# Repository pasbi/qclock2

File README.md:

# qclock2
Code, Schematics, Photos of the WortUhr Hack

The WORTUHR is a clock that displays the current time in form of glowing words.
This is about the German variant.

Note: The instance I got is presumably a cheap copy of a more expensive design https://qlocktwo.com/.

## Original Design

There is a metal cover of size 20cm x 20cm.
25 German words are blanked out.
It has a DC 5V 1A power connector and two buttons (`+`) and (`-`).
The plastic housing is 4 cm thick and encloses the metal sheet completey.
Inside there is a PCB whith 25 LED-groups, one group per word, with varying number of LEDs per group.
There's further two groups with each five LED drivers (transitor and multiple resistors), one IC, a quartz and few other passive components.
After powering the the PCB, the clock displays 12:00 ("ES IST ZWÖLF UHR").
The time can be adjusted using the two buttons.

## Problem

The problem with the original product is that it does reset every time power is disconnected.
That makes it inconvenient to use occasionally.

## Idea

Implement some circuit that synchronizes the time via NTP.

## Implementation

The original driver chip has been unsoldered, the 10 transistors on the board have been soldered to cables and dupont-connectors.

A 8266 and MCP23017 are connected via I²C.
The MCP keeps the time and synchronizes regularly via WIFI and NTP.
Since the watch works at 5V and the 8266 at 3.3V, a two-channel bidirectional logic level converter is required to translate the I²C signals.

Porting the breadboard to a sodered board turned out messy, error-prone and cumbersome.
Ordering a printed PCB seems to be the better choice.

kicad-files can be found in the repo:

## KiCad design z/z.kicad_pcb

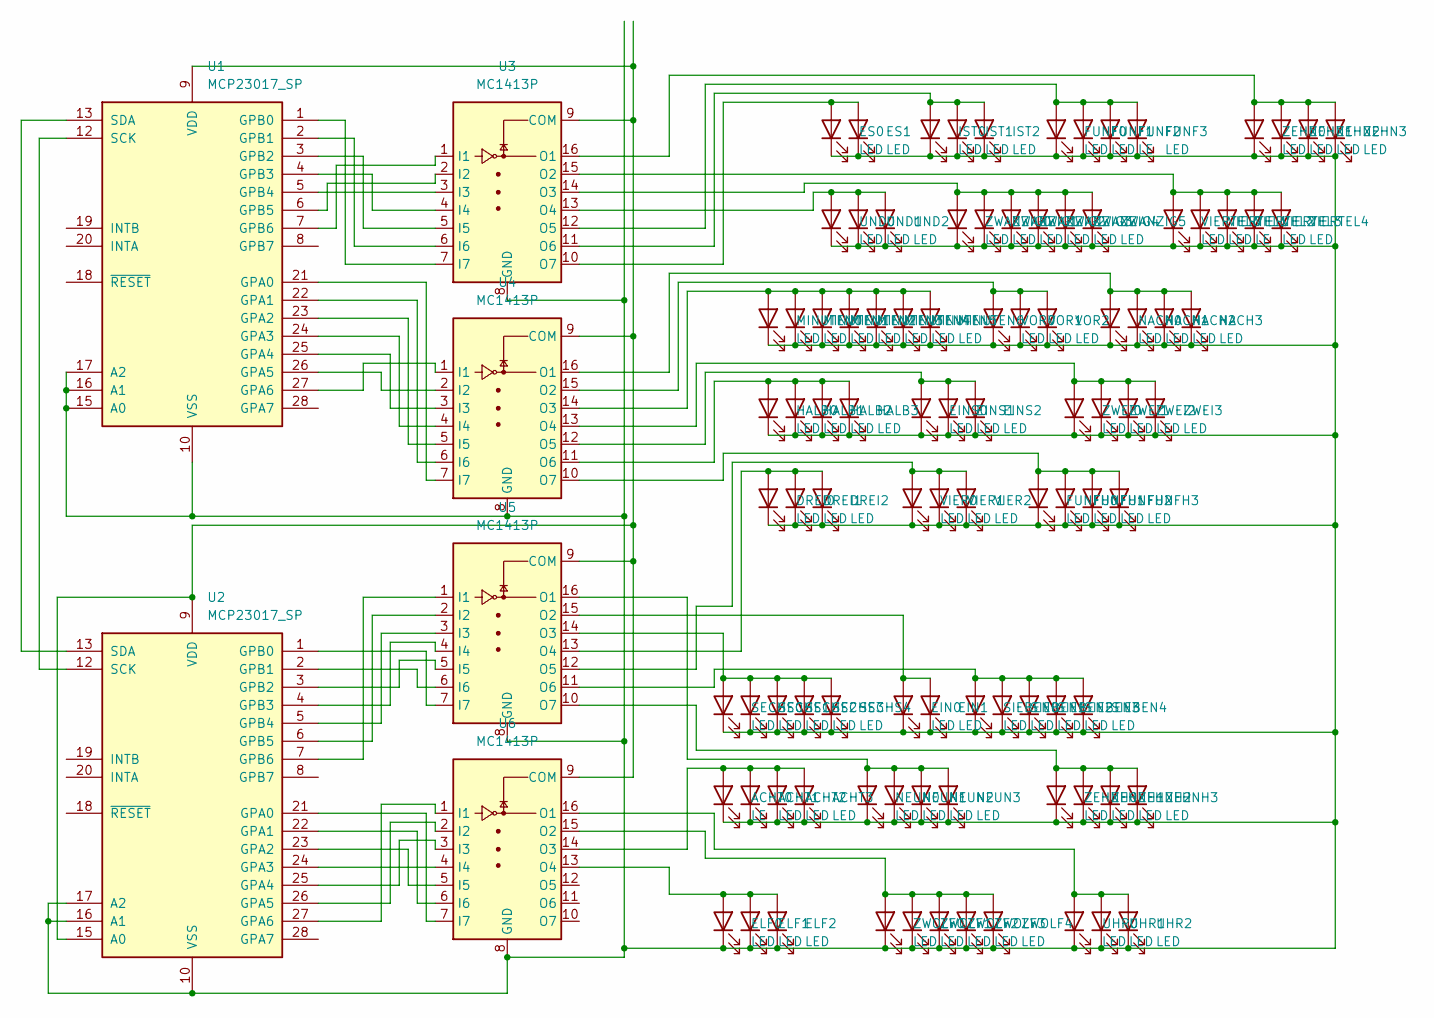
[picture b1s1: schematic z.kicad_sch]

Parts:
ACHT0: LE; LED_D5.0mm_Clear
ACHT1, ACHT2, ACHT3: LED; LED_D5.0mm_Clear
DREI0, DREI1, DREI2: LED; LED_D5.0mm_Clear
EIN0, EIN1: LED; LED_D5.0mm_Clear
EINS0, EINS1, EINS2: LED; LED_D5.0mm_Clear
ELF0, ELF1, ELF2: LED; LED_D5.0mm_Clear
ES0, ES1: LED; LED_D5.0mm_Clear
FUNF0, FUNF1, FUNF3: LED; LED_D5.0mm_Clear
FUNF2: LE; LED_D5.0mm_Clear
FUNFH0, FUNFH1, FUNFH2, FUNFH3: LED; LED_D5.0mm_Clear
HALB0, HALB1, HALB2, HALB3: LED; LED_D5.0mm_Clear
IST0, IST1, IST2: LED; LED_D5.0mm_Clear
MINUTEN0, MINUTEN1, MINUTEN2, MINUTEN3, MINUTEN4, MINUTEN5, MINUTEN6: LED; LED_D5.0mm_Clear
NACH0, NACH1, NACH2, NACH3: LED; LED_D5.0mm_Clear
NEUN0, NEUN1, NEUN2, NEUN3: LED; LED_D5.0mm_Clear
SECHS0, SECHS1, SECHS2, SECHS3, SECHS4: LED; LED_D5.0mm_Clear
SIEBEN0, SIEBEN1, SIEBEN2, SIEBEN3, SIEBEN4: LED; LED_D5.0mm_Clear
U1, U2: MCP23017_SP; DIP-28_W7.62mm
U3, U4, U5, U6: MC1413P; DIP-16_W7.62mm
UHR0, UHR1, UHR2: LED; LED_D5.0mm_Clear
UND0, UND1, UND2: LED; LED_D5.0mm_Clear
VIER0, VIER1, VIER2: LED; LED_D5.0mm_Clear
VIERTEL0, VIERTEL1, VIERTEL3, VIERTEL4: LED; LED_D5.0mm_Clear
VIERTEL2: LE; LED_D5.0mm_Clear
VOR0, VOR1, VOR2: LED; LED_D5.0mm_Clear
ZEHN0, ZEHN1, ZEHN2, ZEHN3: LED; LED_D5.0mm_Clear
ZEHNH0, ZEHNH1, ZEHNH2, ZEHNH3: LED; LED_D5.0mm_Clear
ZWANZIG0, ZWANZIG1, ZWANZIG2, ZWANZIG3, ZWANZIG4, ZWANZIG5: LED; LED_D5.0mm_Clear
ZWEI0, ZWEI1, ZWEI2, ZWEI3: LED; LED_D5.0mm_Clear
ZWOLF0, ZWOLF1, ZWOLF2, ZWOLF3, ZWOLF4: LED; LED_D5.0mm_Clear

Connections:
unnamed: ACHT0.2 (A), ACHT1.2 (A), ACHT2.2 (A), ACHT3.2 (A), U6.14 (O3)
unnamed: DREI0.2 (A), DREI1.2 (A), DREI2.2 (A), U5.13 (O4)
unnamed: EIN0.2 (A), EIN1.2 (A), U5.15 (O2)
unnamed: EINS0.2 (A), EINS1.2 (A), EINS2.2 (A), U4.12 (O5)
unnamed: ELF0.2 (A), ELF1.2 (A), ELF2.2 (A), U6.13 (O4)
unnamed: ES0.2 (A), ES1.2 (A), U3.10 (O7)
unnamed: FUNF0.2 (A), FUNF1.2 (A), FUNF2.2 (A), FUNF3.2 (A), U3.12 (O5)
unnamed: FUNFH0.2 (A), FUNFH1.2 (A), FUNFH2.2 (A), FUNFH3.2 (A), U4.10 (O7)
unnamed: HALB0.2 (A), HALB1.2 (A), HALB2.2 (A), HALB3.2 (A), U4.11 (O6)
unnamed: IST0.2 (A), IST1.2 (A), IST2.2 (A), U3.11 (O6)
unnamed: MINUTEN0.2 (A), MINUTEN1.2 (A), MINUTEN2.2 (A), MINUTEN3.2 (A), MINUTEN4.2 (A), MINUTEN5.2 (A), MINUTEN6.2 (A), U4.14 (O3)
unnamed: NACH0.2 (A), NACH1.2 (A), NACH2.2 (A), NACH3.2 (A), U4.16 (O1)
unnamed: NEUN0.2 (A), NEUN1.2 (A), NEUN2.2 (A), NEUN3.2 (A), U5.16 (O1)
unnamed: SECHS0.2 (A), SECHS1.2 (A), SECHS2.2 (A), SECHS3.2 (A), SECHS4.2 (A), U5.14 (O3)
unnamed: SIEBEN0.2 (A), SIEBEN1.2 (A), SIEBEN2.2 (A), SIEBEN3.2 (A), SIEBEN4.2 (A), U5.11 (O6)
unnamed: U1.3 (GPB2), U3.5 (I5)
unnamed: U1.4 (GPB3), U3.4 (I4)
unnamed: U1.6 (GPB5), U3.2 (I2)
unnamed: U1.9 (VDD), U2.9 (VDD), U2.15 (A0), U3.9 (COM), U4.9 (COM), U5.9 (COM), U6.9 (COM)
unnamed: U1.12 (SCK), U2.12 (SCK)
unnamed: U1.13 (SDA), U2.13 (SDA)
unnamed: U1.22 (GPA1), U4.6 (I6)
unnamed: U1.23 (GPA2), U4.5 (I5)
unnamed: U1.24 (GPA3), U4.4 (I4)
unnamed: U1.25 (GPA4), U4.3 (I3)
unnamed: U1.26 (GPA5), U4.2 (I2)
unnamed: U1.27 (GPA6), U4.1 (I1)
unnamed: U2.1 (GPB0), U5.7 (I7)
unnamed: U2.2 (GPB1), U5.6 (I6)
unnamed: U2.22 (GPA1), U6.6 (I6)
unnamed: U2.23 (GPA2), U6.5 (I5)
unnamed: U2.24 (GPA3), U6.4 (I4)
unnamed: U2.25 (GPA4), U6.3 (I3)
unnamed: U1.7 (GPB6), U3.1 (I1)
unnamed: U1.5 (GPB4), U3.3 (I3)
unnamed: U1.2 (GPB1), U3.6 (I6)
unnamed: U1.1 (GPB0), U3.7 (I7)
unnamed: U1.21 (GPA0), U4.7 (I7)
unnamed: U2.7 (GPB6), U5.1 (I1)
unnamed: U2.6 (GPB5), U5.2 (I2)
unnamed: U2.5 (GPB4), U5.3 (I3)
unnamed: U2.4 (GPB3), U5.4 (I4)
unnamed: U2.3 (GPB2), U5.5 (I5)
unnamed: U5.10 (O7), ZEHNH0.2 (A), ZEHNH1.2 (A), ZEHNH2.2 (A), ZEHNH3.2 (A)
unnamed: U2.27 (GPA6), U6.1 (I1)
unnamed: U2.26 (GPA5), U6.2 (I2)
unnamed: U2.21 (GPA0), U6.7 (I7)
unnamed: U6.16 (O1), UHR0.2 (A), UHR1.2 (A), UHR2.2 (A)
unnamed: U3.13 (O4), UND0.2 (A), UND1.2 (A), UND2.2 (A)
unnamed: U5.12 (O5), VIER0.2 (A), VIER1.2 (A), VIER2.2 (A)
unnamed: U3.15 (O2), VIERTEL0.2 (A), VIERTEL1.2 (A), VIERTEL2.2 (A), VIERTEL3.2 (A), VIERTEL4.2 (A)
unnamed: U4.15 (O2), VOR0.2 (A), VOR1.2 (A), VOR2.2 (A)
unnamed: ACHT0.1 (K), ACHT1.1 (K), ACHT2.1 (K), ACHT3.1 (K), DREI0.1 (K), DREI1.1 (K), DREI2.1 (K), EIN0.1 (K), EIN1.1 (K), EINS0.1 (K), EINS1.1 (K), EINS2.1 (K), ELF0.1 (K), ELF1.1 (K), ELF2.1 (K), ES0.1 (K), ES1.1 (K), FUNF0.1 (K), FUNF1.1 (K), FUNF2.1 (K), FUNF3.1 (K), FUNFH0.1 (K), FUNFH1.1 (K), FUNFH2.1 (K), FUNFH3.1 (K), HALB0.1 (K), HALB1.1 (K), HALB2.1 (K), HALB3.1 (K), IST0.1 (K), IST1.1 (K), IST2.1 (K), MINUTEN0.1 (K), MINUTEN1.1 (K), MINUTEN2.1 (K), MINUTEN3.1 (K), MINUTEN4.1 (K), MINUTEN5.1 (K), MINUTEN6.1 (K), NACH0.1 (K), NACH1.1 (K), NACH2.1 (K), NACH3.1 (K), NEUN0.1 (K), NEUN1.1 (K), NEUN2.1 (K), NEUN3.1 (K), SECHS0.1 (K), SECHS1.1 (K), SECHS2.1 (K), SECHS3.1 (K), SECHS4.1 (K), SIEBEN0.1 (K), SIEBEN1.1 (K), SIEBEN2.1 (K), SIEBEN3.1 (K), SIEBEN4.1 (K), U1.10 (VSS), U1.15 (A0), U1.16 (A1), U1.17 (A2), U2.10 (VSS), U2.16 (A1), U2.17 (A2), U3.8 (GND), U4.8 (GND), U5.8 (GND), U6.8 (GND), UHR0.1 (K), UHR1.1 (K), UHR2.1 (K), UND0.1 (K), UND1.1 (K), UND2.1 (K), VIER0.1 (K), VIER1.1 (K), VIER2.1 (K), VIERTEL0.1 (K), VIERTEL1.1 (K), VIERTEL2.1 (K), VIERTEL3.1 (K), VIERTEL4.1 (K), VOR0.1 (K), VOR1.1 (K), VOR2.1 (K), ZEHN0.1 (K), ZEHN1.1 (K), ZEHN2.1 (K), ZEHN3.1 (K), ZEHNH0.1 (K), ZEHNH1.1 (K), ZEHNH2.1 (K), ZEHNH3.1 (K), ZWANZIG0.1 (K), ZWANZIG1.1 (K), ZWANZIG2.1 (K), ZWANZIG3.1 (K), ZWANZIG4.1 (K), ZWANZIG5.1 (K), ZWEI0.1 (K), ZWEI1.1 (K), ZWEI2.1 (K), ZWEI3.1 (K), ZWOLF0.1 (K), ZWOLF1.1 (K), ZWOLF2.1 (K), ZWOLF3.1 (K), ZWOLF4.1 (K)
unnamed: U3.16 (O1), ZEHN0.2 (A), ZEHN1.2 (A), ZEHN2.2 (A), ZEHN3.2 (A)
unnamed: U3.14 (O3), ZWANZIG0.2 (A), ZWANZIG1.2 (A), ZWANZIG2.2 (A), ZWANZIG3.2 (A), ZWANZIG4.2 (A), ZWANZIG5.2 (A)
unnamed: U4.13 (O4), ZWEI0.2 (A), ZWEI1.2 (A), ZWEI2.2 (A), ZWEI3.2 (A)
unnamed: U6.15 (O2), ZWOLF0.2 (A), ZWOLF1.2 (A), ZWOLF2.2 (A), ZWOLF3.2 (A), ZWOLF4.2 (A)

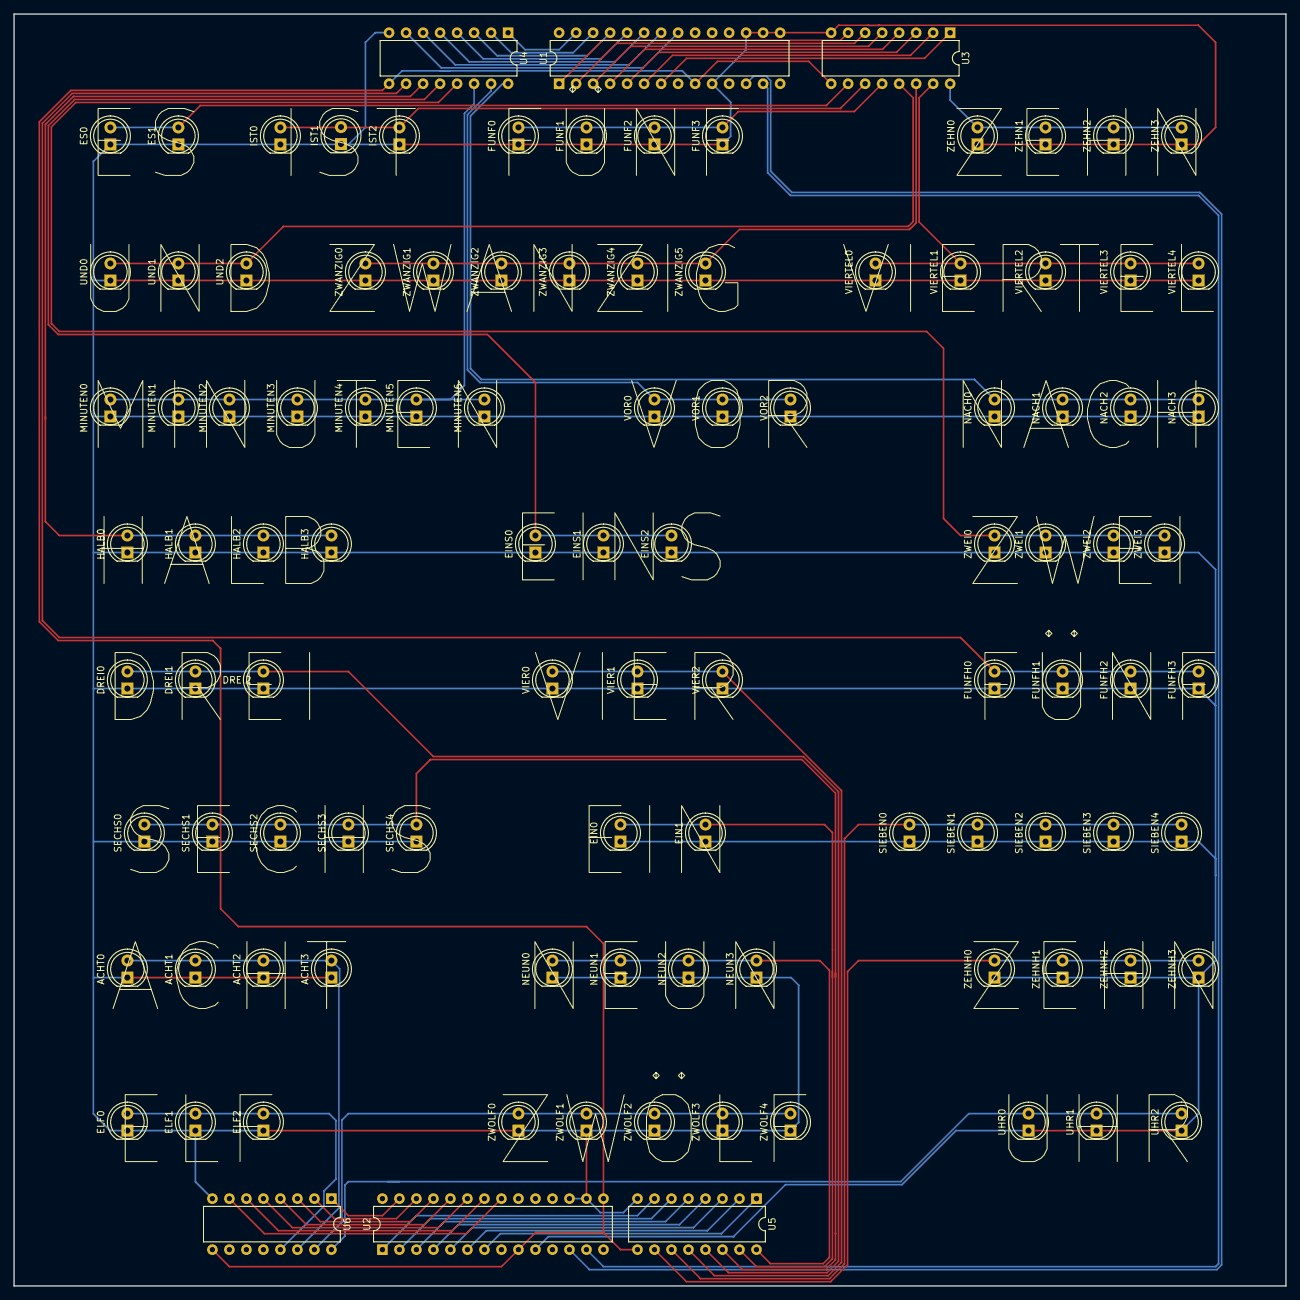
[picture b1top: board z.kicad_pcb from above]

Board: 2 copper layers, 190.0 x 190.0 mm, 103 parts (0 on the bottom side), 57 nets.

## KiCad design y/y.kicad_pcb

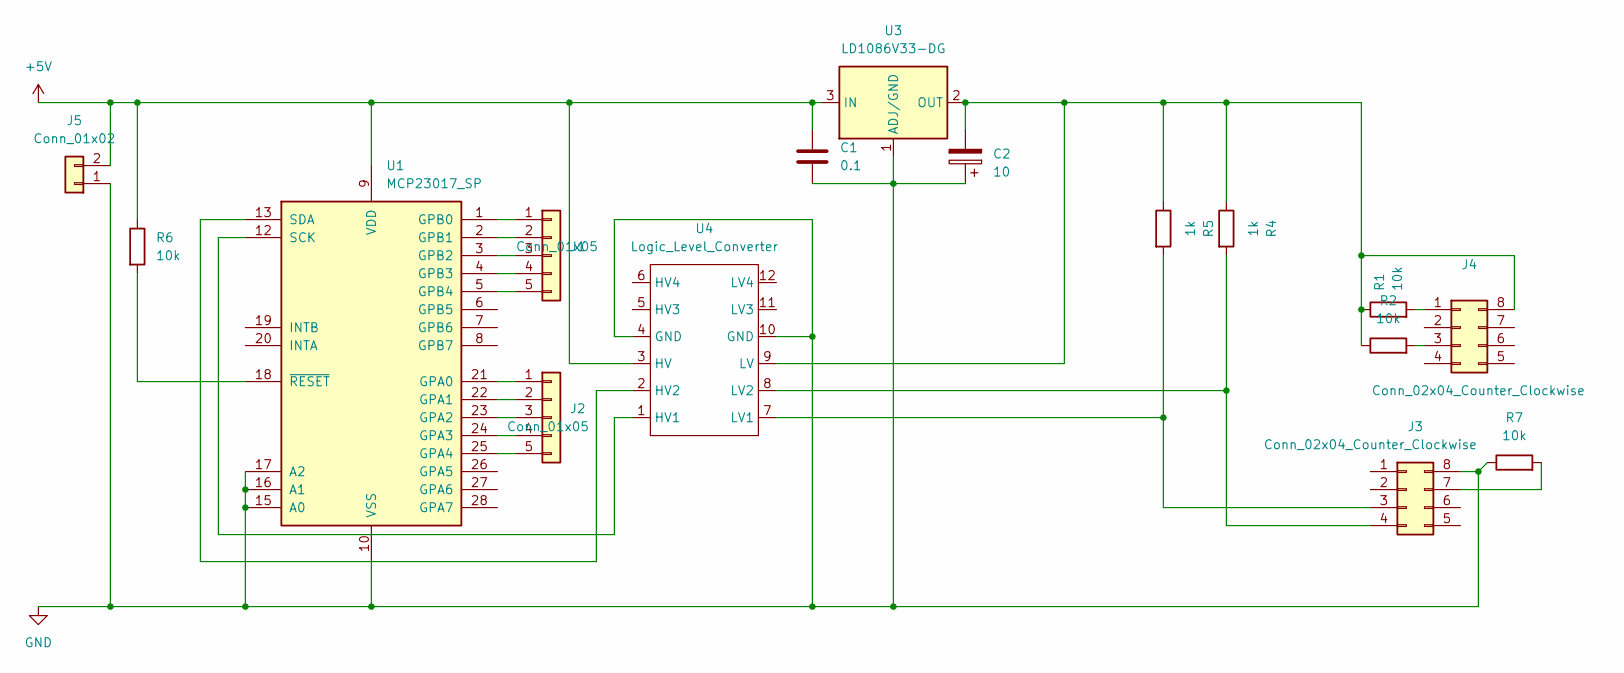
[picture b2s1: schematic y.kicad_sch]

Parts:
C1: 0.1; C_Disc_D11.0mm_W5.0mm_P5.00mm
C2: 10; CP_Radial_Tantal_D4.5mm_P2.50mm
J1, J2: Conn_01x05; PinHeader_1x05_P2.54mm_Vertical
J3, J4: Conn_02x04_Counter_Clockwise; PinSocket_2x04_P2.54mm_Vertical
J5: Conn_01x02; PinSocket_1x02_P2.54mm_Vertical
R1, R2, R6, R7: 10k; R_Axial_DIN0207_L6.3mm_D2.5mm_P7.62mm_Horizontal
R4, R5: 1k; R_Axial_DIN0207_L6.3mm_D2.5mm_P7.62mm_Horizontal
U1: MCP23017_SP; DIP-28_W7.62mm
U3: LD1086V33-DG; TO-220-3_Vertical
U4: Logic_Level_Converter; Logic Level Converter

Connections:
+5V: C1.1, J5.2, R6.1, U1.9 (VDD), U3.3 (IN), U4.3 (HV)
GND: C1.2, C2.1, J3.8 (GND), J5.1, R7.1, U1.10 (VSS), U1.15 (A0), U1.16 (A1), U1.17 (A2), U3.1 (ADJ/GND), U4.4 (GND), U4.10 (GND)
unnamed: C2.2, J4.8 (VCC), R1.1, R2.1, R4.1, R5.1, U3.2 (OUT), U4.9 (LV)
unnamed: J1.1, U1.1 (GPB0)
unnamed: J1.2, U1.2 (GPB1)
unnamed: J1.3, U1.3 (GPB2)
unnamed: J1.4, U1.4 (GPB3)
unnamed: J1.5, U1.5 (GPB4)
unnamed: J2.1, U1.21 (GPA0)
unnamed: J2.2, U1.22 (GPA1)
unnamed: J2.3, U1.23 (GPA2)
unnamed: J2.4, U1.24 (GPA3)
unnamed: J2.5, U1.25 (GPA4)
unnamed: J3.4 (IO4), R4.2, U4.8 (LV2)
unnamed: J4.1 (RST), R1.2
unnamed: J4.3 (EN), R2.2
unnamed: J3.3 (IO5), R5.2, U4.7 (LV1)
unnamed: R6.2, U1.18 (~RESET)
unnamed: J3.7 (IO15), R7.2
unnamed: U1.12 (SCK), U4.1 (HV1)
unnamed: U1.13 (SDA), U4.2 (HV2)

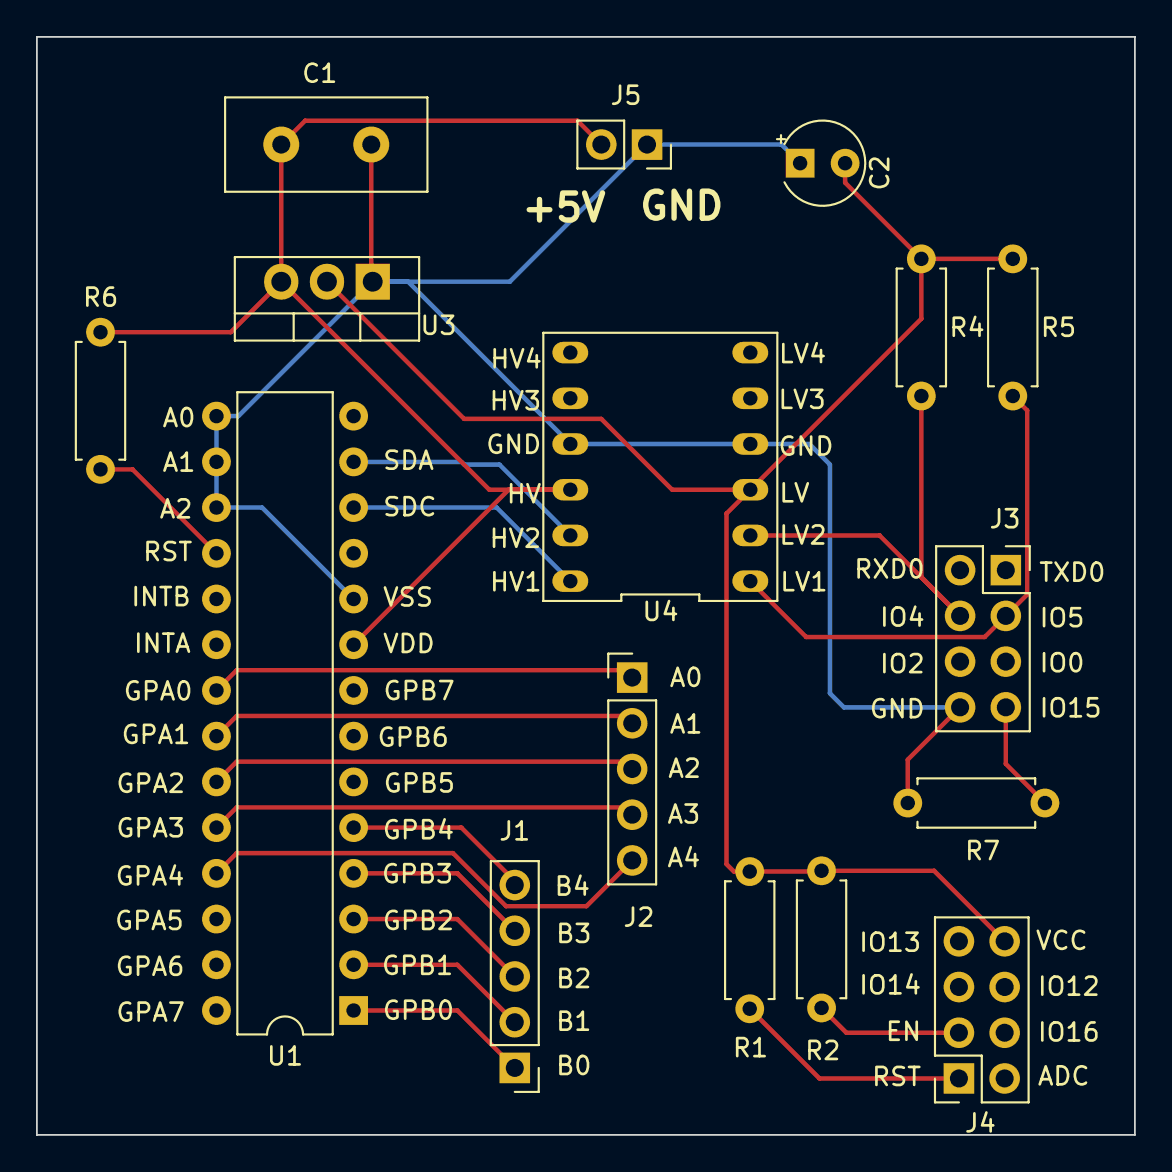
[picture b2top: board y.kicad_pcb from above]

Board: 2 copper layers, 61.0 x 61.0 mm, 16 parts (0 on the bottom side), 21 nets.

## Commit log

2022-02-13 add code
2022-02-13 add pictures
2022-02-19 more images
2022-02-19 move secrets into separate file
2022-02-19 add pcb files
2022-02-19 add more images
2024-12-30 add alternative layout z
2024-12-30 add main.py
